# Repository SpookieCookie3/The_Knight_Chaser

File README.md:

# The_Knight_Chaser
An LED chaser on a PCB shaped into the head of the Knight from the game Hollow Knight using the guides for Blinky @ Hack Club Blueprint. It has a few precepts of Zote from the game and some art too.
# 3D view

# Shematic

# BOM

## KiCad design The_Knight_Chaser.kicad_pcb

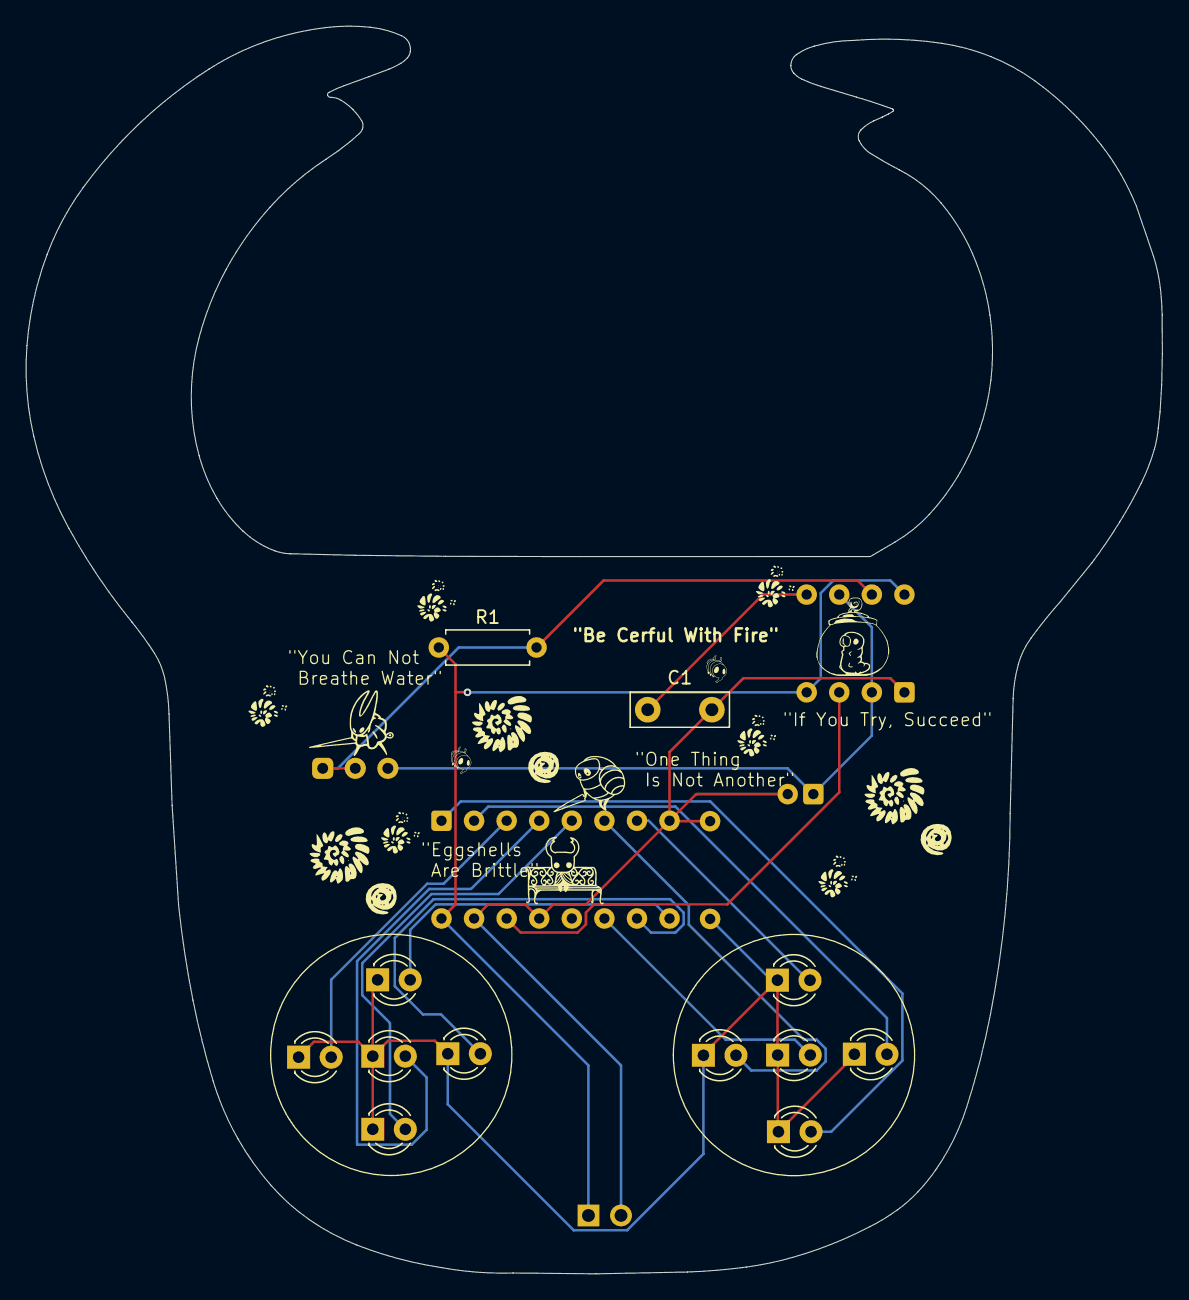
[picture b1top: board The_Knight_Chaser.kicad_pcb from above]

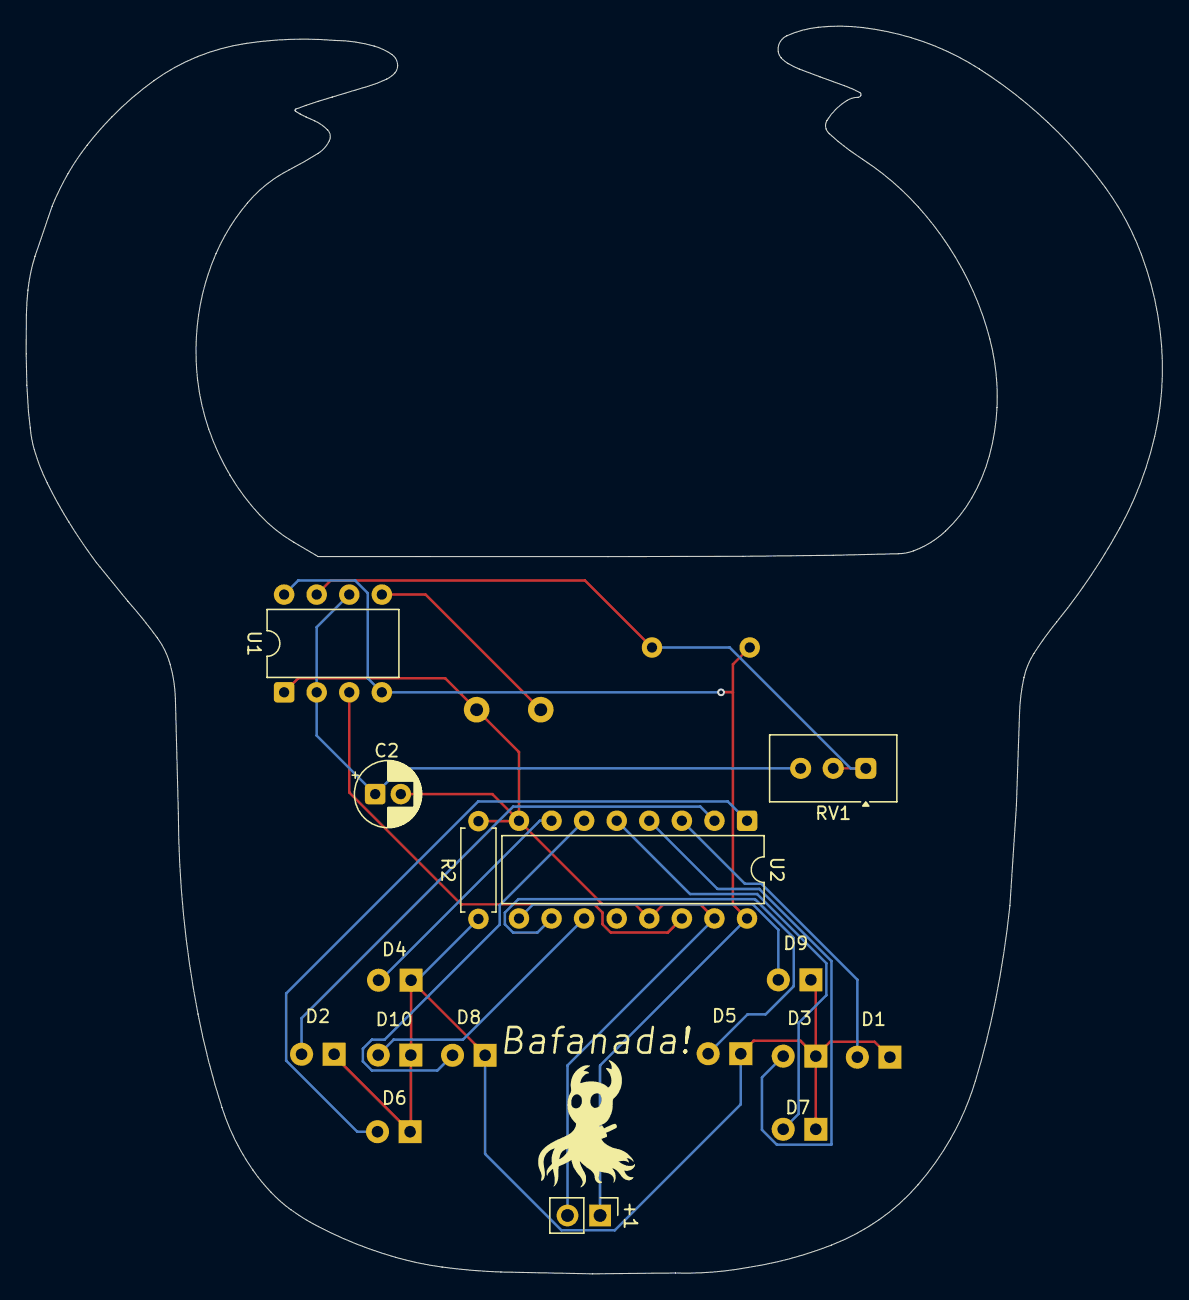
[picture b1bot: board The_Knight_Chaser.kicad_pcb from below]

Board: 2 copper layers, 88.6 x 97.3 mm, 18 parts (6 on the bottom side), 17 nets.

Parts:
+1: -; PinHeader_1x02_P2.54mm_Vertical
C1: 0.01 uF; C_Disc_D7.5mm_W2.5mm_P5.00mm
C2: 1 uF; CP_Radial_D5.0mm_P2.00mm
D1, D2, D3, D4, D5, D6, D7, D8, D9, D10: LED; LED_D3.0mm
R1: 1k; R_Axial_DIN0207_L6.3mm_D2.5mm_P7.62mm_Horizontal
R2: 220; R_Axial_DIN0207_L6.3mm_D2.5mm_P7.62mm_Horizontal
RV1: 50k; Potentiometer_Vishay_T93YA_Vertical
U1: NE555P; DIP-8_W7.62mm
U2: 4017; DIP-16_W7.62mm

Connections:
+5V: +1.1, R1.1, U1.4 (~RST), U1.8 (VCC), U2.16 (VDD)
GND: +1.2, C1.2, C2.2, R2.2, U1.1 (GND), U2.8 (VSS), U2.13 (CKEN), U2.15 (Reset)
unnamed: D1.2 (A), U2.3 (Q0)
unnamed: D1.1 (K), D2.1 (K), D3.1 (K), D4.1 (K), D5.1 (K), D6.1 (K), D7.1 (K), D8.1 (K), D9.1 (K), D10.1 (K), R2.1
unnamed: D2.2 (A), U2.2 (Q1)
unnamed: D3.2 (A), U2.4 (Q2)
unnamed: D4.2 (A), U2.7 (Q3)
unnamed: D5.2 (A), U2.10 (Q4)
unnamed: D6.2 (A), U2.1 (Q5)
unnamed: D7.2 (A), U2.5 (Q6)
unnamed: D8.2 (A), U2.6 (Q7)
unnamed: D9.2 (A), U2.9 (Q8)
unnamed: D10.2 (A), U2.11 (Q9)
unnamed: C1.1, U1.5 (CONT)
unnamed: R1.2, RV1.1, RV1.2, U1.7 (DIS)
OUT: U1.3 (OUT), U2.14 (CLK)
TR: C2.1, RV1.3, U1.2 (TRIG), U1.6 (THR)
